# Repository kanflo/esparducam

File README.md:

# Esparducam
#### A low cost network camera for the ESP8266

This repository contains code and schematics to build a development board joining the ESP8266 with the [Arducam Mini](http://www.arducam.com/arducam-mini-released/) module. Build surveillance cameras, read your water meter, attach one to your kite.

The board design allows for small breakout boards to be attached. There currently is [a breakout board the the RFM69C](https://github.com/kanflo/esparducam/tree/master/hardware/ism-boardlet), [an ESP12 board with pogo pins](https://github.com/kanflo/esparducam/tree/master/hardware/esp-pinlet) and [one for swappable ESP12 modules](https://github.com/kanflo/esparducam/tree/master/hardware/esp-boardlet).

Oh, the accompanying blog posts are [here](http://johan.kanflo.com/building-a-low-cost-wifi-camera/), [here](http://johan.kanflo.com/a-versatile-esp8266-development-board/) and [here](http://johan.kanflo.com/esparducam-mini/).

### Usage

Clone the ESP Open RTOS repository. See the documentation for how to add your SSID name and password.

```
git clone --recursive https://github.com/Superhouse/esp-open-rtos.git
```

Add nedded extra modules to ESP Open RTOS ("EOR"):

```
cd esp-open-rtos/extras
git clone https://github.com/kanflo/eor-spi.git spi
git clone https://github.com/kanflo/eor-http-upload.git http-upload
```

Someday I'll start using the native EOR SPI driver, you have to bear with me for now :)

Set the environment variable ```$EOR_ROOT```to point to your EOR repository:

```
export EOR_ROOT=/path/to/esp-open-rtos
```

Clone this repository, make and flash:

```
git clone --recursive https://github.com/kanflo/esparducam.git
cd esparducam
make -j8 && make flash
```

The repository is preconfigured for the Esparducam board. Check ```config.h``` for building for the Esparducam Mini.

When flashing has completed, open a serial terminal to learn the IP number of your board. Open a web brower, point it to your IP and an image should be captured and displayed. While in the serial terminal, type ```help``` for a list of supported commands.

Start the python script ```server.py``` and type ```upload:<your IP>``` to capture, upload and display an image on your computer.

If you connect a [PIR module](http://www.ebay.com/sch/i.html?_trksid=PIR+module.TRS0&_nkw=PIR+module&_sacat=0) [eBay] to the JST connector of the Esparducam board you can use the command ```motion:on:<your ip>``` to have the board capture and upload an image when motion is detected. The Mini variant has a 3 pin slot for attaching a PIR but you need to check the pinout carefully. It should be VCC, OUT, GND but I have seen other combinations.

### Limitations

This is work in progress and there is currently very little error handling. Simultaneous clients will break the camera demo.

-

Licensed under the MIT license. Have fun!

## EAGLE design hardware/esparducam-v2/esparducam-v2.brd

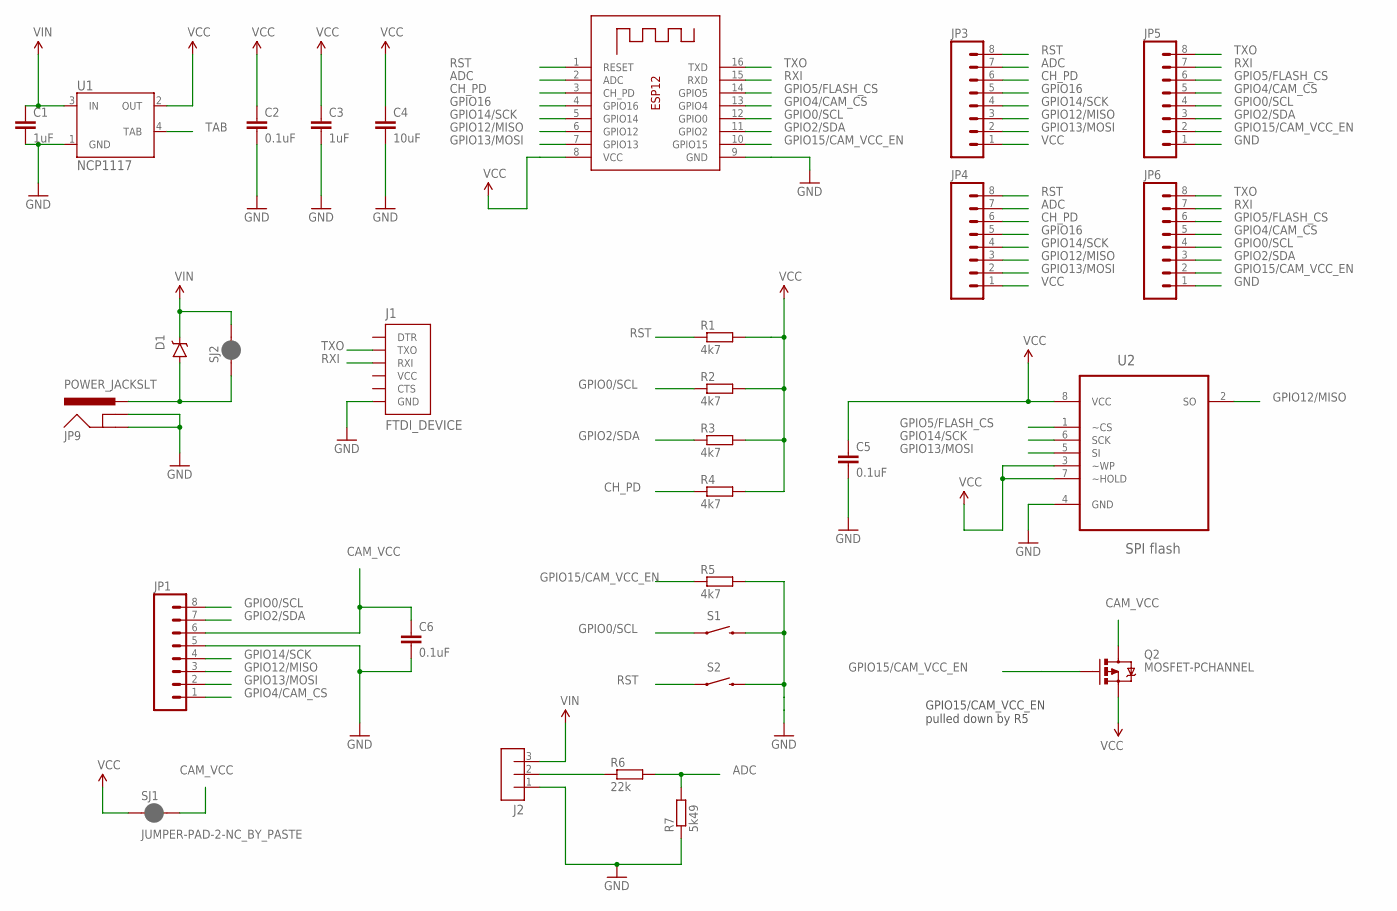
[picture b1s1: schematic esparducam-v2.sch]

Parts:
C1, C3: 1uF; 0603-CAP
C2, C5, C6: 0.1uF; 0603-CAP
C4: 10uF; 0603-CAP
D1: DIODE-SCHOTTKYSOD-123FL; SOD-123FL
J1: FTDI_DEVICE; FTDI
J2: JST_ZH_3PIN
JP1, JP3, JP4, JP5, JP6: M08; 1X08_ROUND
JP9: POWER_JACKSLT; POWER_JACK_SLOT
Q2: MOSFET-PCHANNEL; SOT23-3
R1, R2, R3, R4, R5: 4k7; R0603
R6: 22k; R0603
R7: 5k49; R0603
S1, S2: SWITCH-MOMENTARY-2SMD-1101NE; TACTILE-SWITCH-1101NE
SJ1, SJ2: JUMPER-PAD-2-NC_BY_PASTE; PAD-JUMPER-2-NC_BY_PASTE_YES_SILK
U1: NCP1117; SOT223
U2: SPI flash; SOIC127P600X175-8N
X1: ESP-12

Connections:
ADC: JP3.7, JP4.7, R6.2, R7.2, X1.2 (ADC)
CAM_VCC: C6.1, JP1.6, Q2.3 (D), SJ1.2
CH_PD: JP3.6, JP4.6, R4.1, X1.3 (CH_PD)
GND: C1.2, C2.2, C3.2, C4.2, C5.2, C6.2, J1.GND, J2.1, JP1.5, JP5.1, JP6.1, JP9.GND@1 (GNDBREAK), JP9.GND@2 (GND), R5.2, R7.1, S1.2, S2.2, U1.1 (GND), U2.4 (GND), X1.9 (GND)
GPIO0/SCL: JP1.8, JP5.4, JP6.4, R2.1, S1.1, X1.12 (GPIO0)
GPIO2/SDA: JP1.7, JP5.3, JP6.3, R3.1, X1.11 (GPIO2)
GPIO4/CAM_CS: JP1.1, JP5.5, JP6.5, X1.13 (GPIO4)
GPIO5/FLASH_CS: JP5.6, JP6.6, U2.1 (~CS), X1.14 (GPIO5)
GPIO12/MISO: JP1.3, JP3.3, JP4.3, U2.2 (SO), X1.6 (GPIO12)
GPIO13/MOSI: JP1.2, JP3.2, JP4.2, U2.5 (SI), X1.7 (GPIO13)
GPIO14/SCK: JP1.4, JP3.4, JP4.4, U2.6 (SCK), X1.5 (GPIO14)
GPIO15/CAM_VCC_EN: JP5.2, JP6.2, Q2.1 (G), R5.1, X1.10 (GPIO15)
GPIO16: JP3.5, JP4.5, X1.4 (GPIO16)
unnamed: J2.2, R6.1
unnamed: D1.A, JP9.PWR, SJ2.1
RST: JP3.8, JP4.8, R1.1, S2.1, X1.1 (RESET)
RXI: J1.RXI, JP5.7, JP6.7, X1.15 (RXD)
TAB: U1.4 (TAB)
TXO: J1.TXO, JP5.8, JP6.8, X1.16 (TXD)
VCC: C2.1, C3.1, C4.1, C5.1, JP3.1, JP4.1, Q2.2 (S), R1.2, R2.2, R3.2, R4.2, SJ1.1, U1.2 (OUT), U2.3 (~WP), U2.7 (~HOLD), U2.8 (VCC), X1.8 (VCC)
VIN: C1.1, D1.C, J2.3, SJ2.2, U1.3 (IN)

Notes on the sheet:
GPIO15/CAM_VCC_EN pulled down by R5

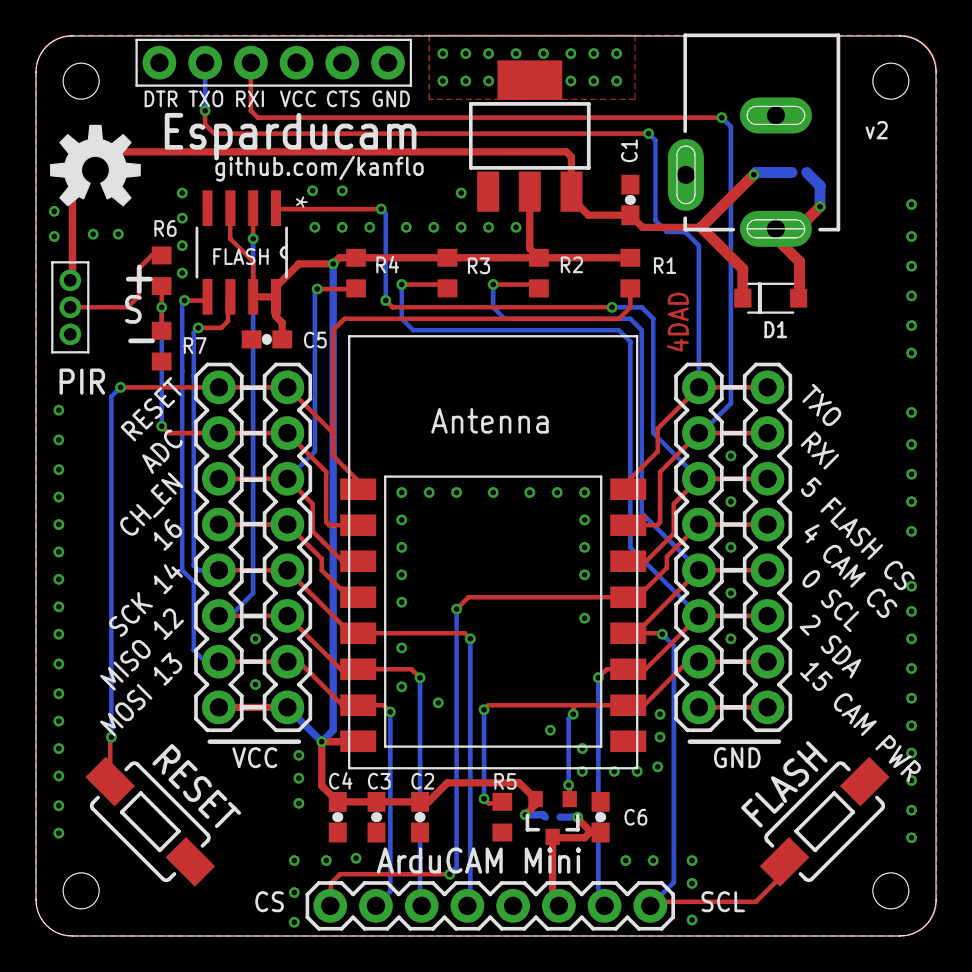
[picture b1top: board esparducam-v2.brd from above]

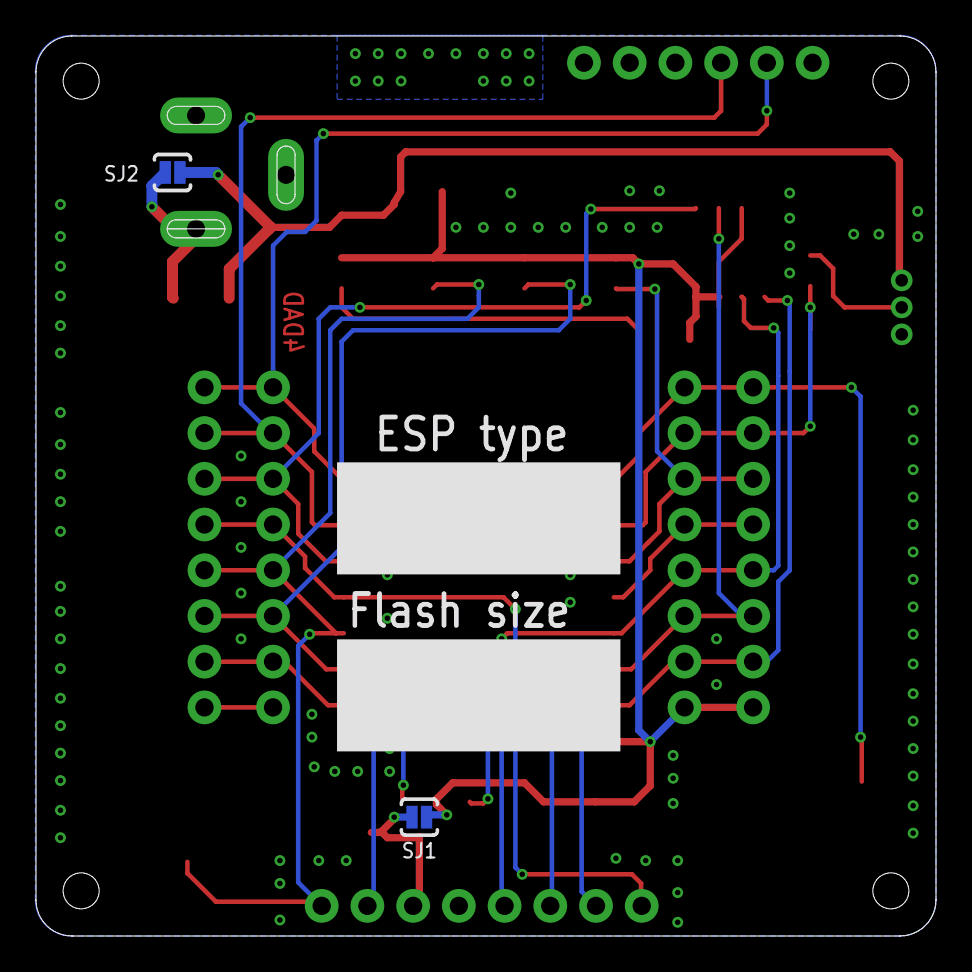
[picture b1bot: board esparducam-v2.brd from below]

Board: 2 copper layers, 50.0 x 50.0 mm, 31 parts (2 on the bottom side), 20 nets.

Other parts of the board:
U$1: OSHW-LOGO-M

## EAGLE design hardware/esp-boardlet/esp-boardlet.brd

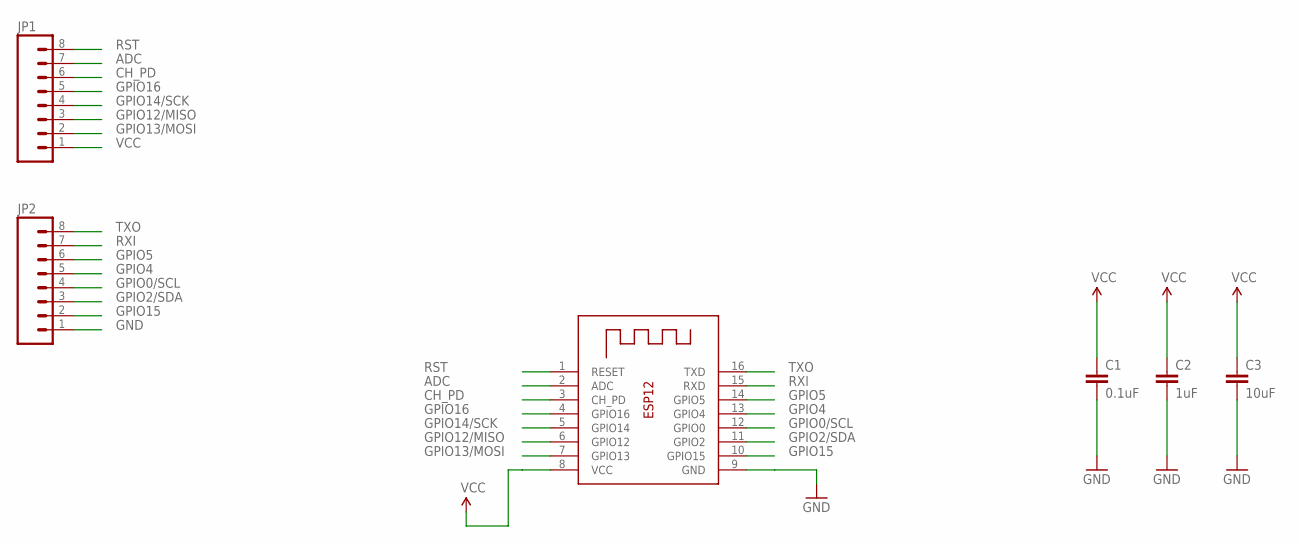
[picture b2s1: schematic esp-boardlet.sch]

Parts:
C1: 0.1uF; 0603-CAP
C2: 1uF; 0603-CAP
C3: 10uF; 0603-CAP
JP1, JP2: M08; 1X08_ROUND
X1: ESP-12

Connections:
ADC: JP1.7, X1.2 (ADC)
CH_PD: JP1.6, X1.3 (CH_PD)
GND: C1.2, C2.2, C3.2, JP2.1, X1.9 (GND)
GPIO0/SCL: JP2.4, X1.12 (GPIO0)
GPIO2/SDA: JP2.3, X1.11 (GPIO2)
GPIO4: JP2.5, X1.13 (GPIO4)
GPIO5: JP2.6, X1.14 (GPIO5)
GPIO12/MISO: JP1.3, X1.6 (GPIO12)
GPIO13/MOSI: JP1.2, X1.7 (GPIO13)
GPIO14/SCK: JP1.4, X1.5 (GPIO14)
GPIO15: JP2.2, X1.10 (GPIO15)
GPIO16: JP1.5, X1.4 (GPIO16)
RST: JP1.8, X1.1 (RESET)
RXI: JP2.7, X1.15 (RXD)
TXO: JP2.8, X1.16 (TXD)
VCC: C1.1, C2.1, C3.1, JP1.1, X1.8 (VCC)

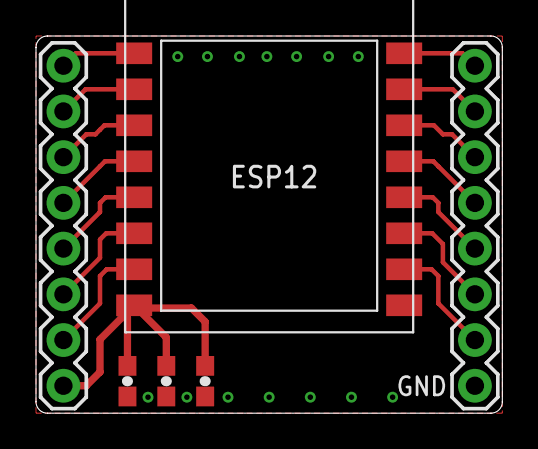
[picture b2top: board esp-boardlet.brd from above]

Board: 2 copper layers, 25.9 x 21.0 mm, 7 parts (1 on the bottom side), 16 nets.

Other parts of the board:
U$1: OSHW-LOGO-M

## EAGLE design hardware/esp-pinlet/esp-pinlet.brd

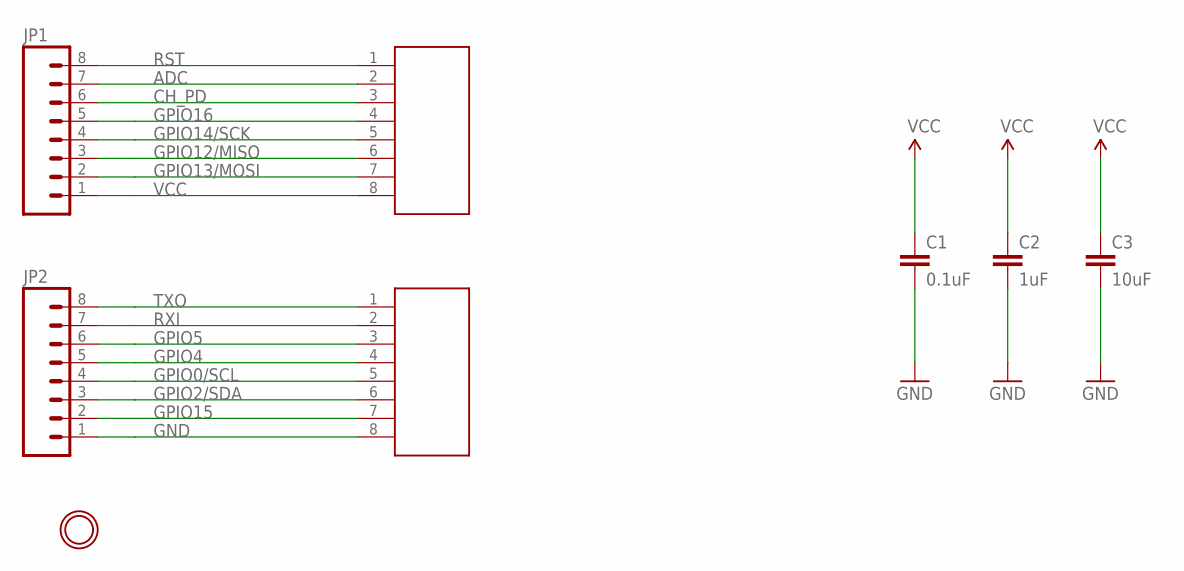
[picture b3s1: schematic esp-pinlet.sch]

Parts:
C1: 0.1uF; 0603-CAP
C2: 1uF; 0603-CAP
C3: 10uF; 0603-CAP
JP1, JP2: M08; 1X08_ROUND
U$2, U$3: 82XMM_POGO_PIN; 8X2MM_POGO_PIN
U$6: MOUNTINGHOLE2.0; MOUNTINGHOLE_2.0_PLATED

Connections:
ADC: JP1.7, U$2.2
CH_PD: JP1.6, U$2.3
GND: C1.2, C2.2, C3.2, JP2.1, U$3.8
GPIO0/SCL: JP2.4, U$3.5
GPIO2/SDA: JP2.3, U$3.6
GPIO4: JP2.5, U$3.4
GPIO5: JP2.6, U$3.3
GPIO12/MISO: JP1.3, U$2.6
GPIO13/MOSI: JP1.2, U$2.7
GPIO14/SCK: JP1.4, U$2.5
GPIO15: JP2.2, U$3.7
GPIO16: JP1.5, U$2.4
RST: JP1.8, U$2.1
RXI: JP2.7, U$3.2
TXO: JP2.8, U$3.1
VCC: C1.1, C2.1, C3.1, JP1.1, U$2.8

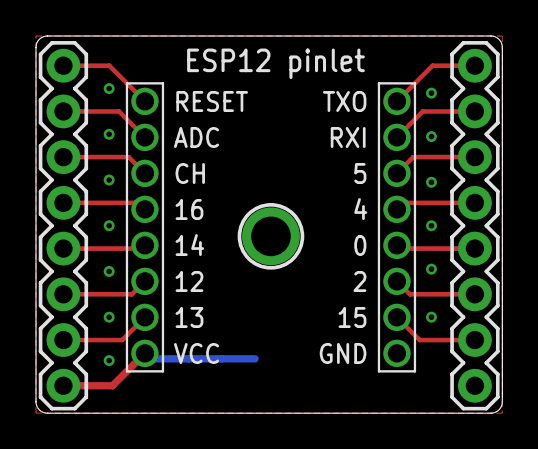
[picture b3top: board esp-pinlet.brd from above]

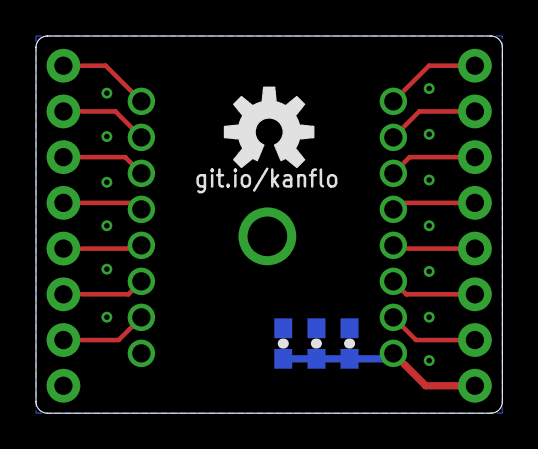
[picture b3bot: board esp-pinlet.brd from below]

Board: 2 copper layers, 25.9 x 21.0 mm, 9 parts (4 on the bottom side), 16 nets.

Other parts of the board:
U$1: OSHW-LOGO-M

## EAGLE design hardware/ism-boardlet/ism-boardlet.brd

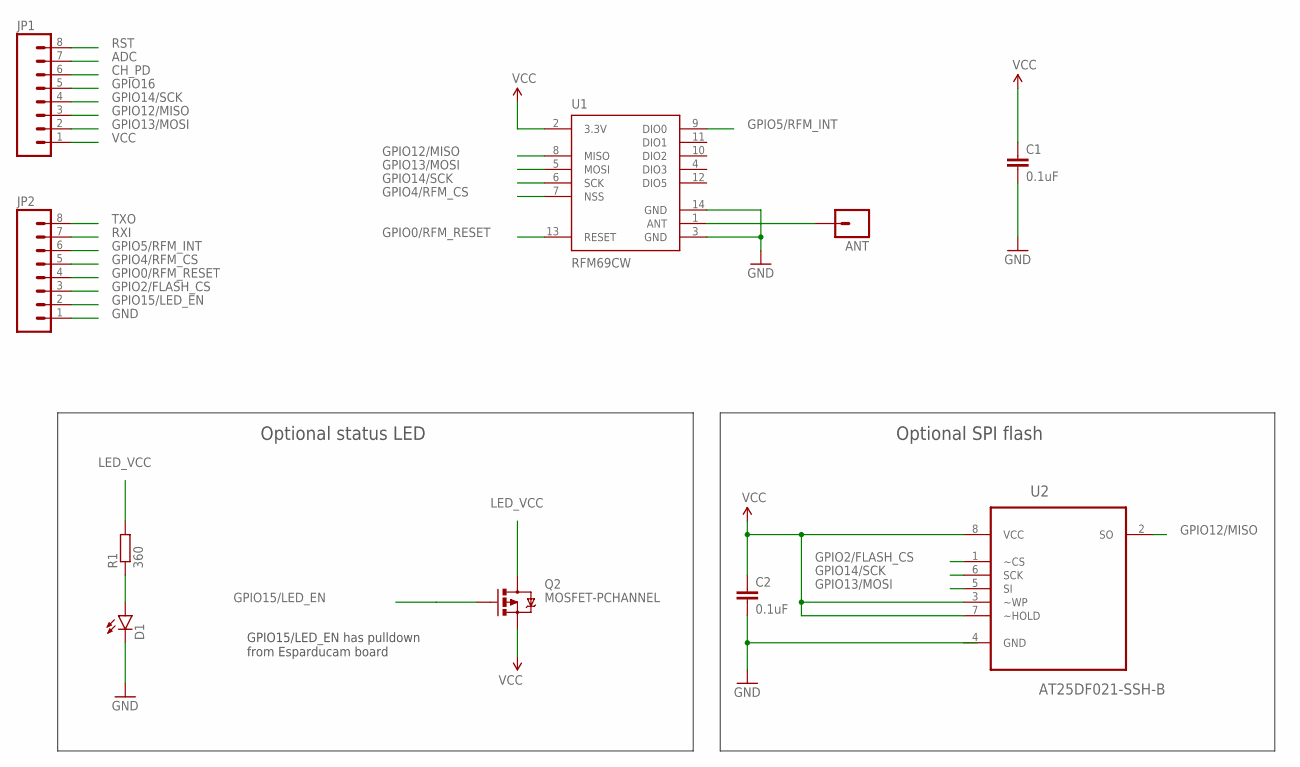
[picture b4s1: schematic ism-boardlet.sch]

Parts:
ANT: M01PTH; 1X01
C1, C2: 0.1uF; 0603-CAP
D1: LED0603; LED-0603
JP1, JP2: M08; 1X08_ROUND
Q2: MOSFET-PCHANNEL; SOT23-3
R1: 360; R0603
U1: RFM69CW; RFM69CW-XXXS2
U2: AT25DF021-SSH-B; SOIC127P600X175-8N

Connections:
ADC: JP1.7
CH_PD: JP1.6
GND: C1.2, C2.2, D1.C, JP2.1, U1.3 (GND), U1.14 (GND)
GPIO0/RFM_RESET: JP2.4, U1.13 (RESET)
GPIO2/FLASH_CS: JP2.3, U2.1 (~CS)
GPIO4/RFM_CS: JP2.5, U1.7 (NSS)
GPIO5/RFM_INT: JP2.6, U1.9 (DIO0)
GPIO12/MISO: JP1.3, U1.8 (MISO), U2.2 (SO)
GPIO13/MOSI: JP1.2, U1.5 (MOSI), U2.5 (SI)
GPIO14/SCK: JP1.4, U1.6 (SCK), U2.6 (SCK)
GPIO15/LED_EN: JP2.2, Q2.1 (G)
GPIO16: JP1.5
LED_VCC: Q2.3 (D), R1.2
unnamed: D1.A, R1.1
unnamed: ANT.1, U1.1 (ANT)
RST: JP1.8
RXI: JP2.7
TXO: JP2.8
VCC: C1.1, C2.1, JP1.1, Q2.2 (S), U1.2 (3.3V), U2.3 (~WP), U2.7 (~HOLD), U2.8 (VCC)

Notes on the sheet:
GPIO15/LED_EN has pulldown from Esparducam board
Optional status LED
Optional SPI flash

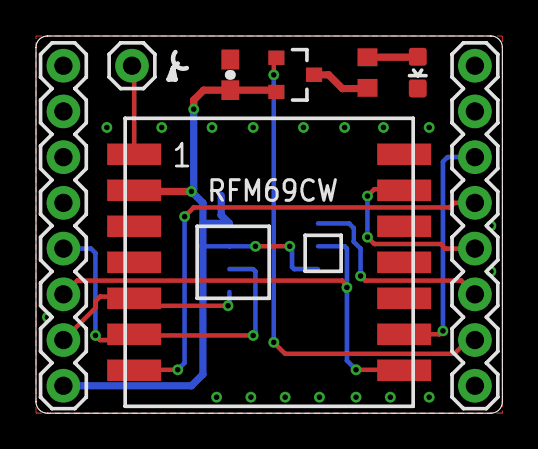
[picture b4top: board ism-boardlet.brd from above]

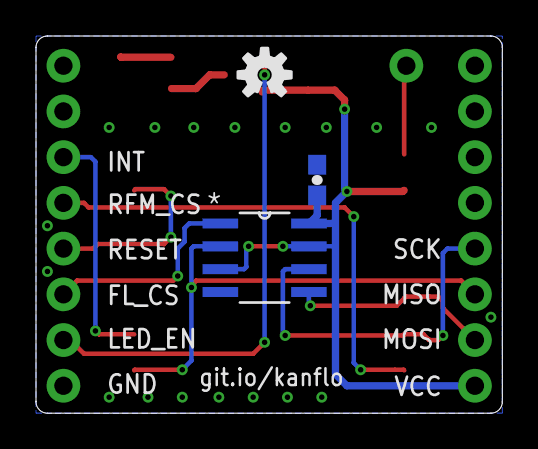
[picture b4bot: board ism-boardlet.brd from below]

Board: 2 copper layers, 25.9 x 21.0 mm, 11 parts (3 on the bottom side), 13 nets.

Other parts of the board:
U$2: OSHW-LOGO-S

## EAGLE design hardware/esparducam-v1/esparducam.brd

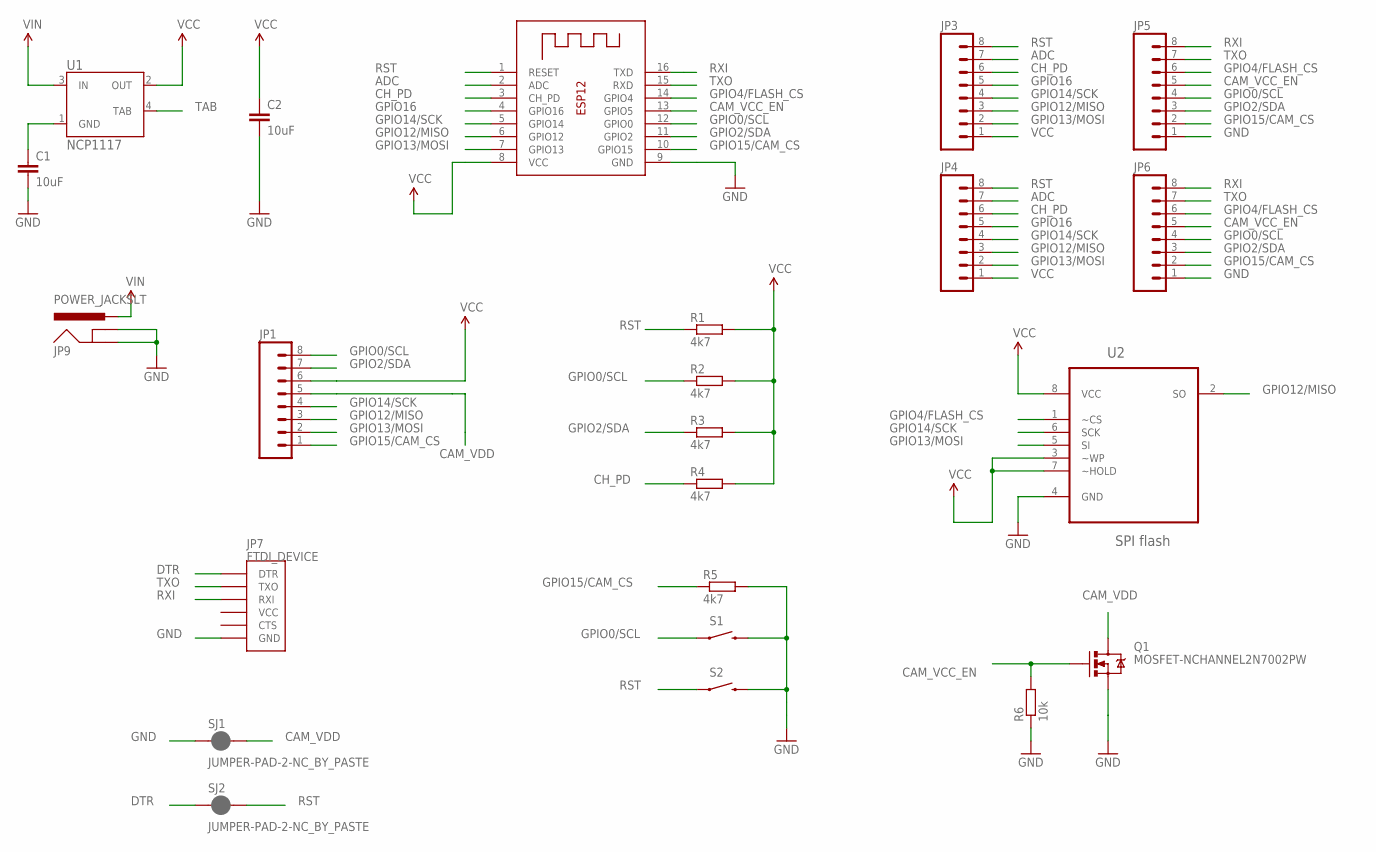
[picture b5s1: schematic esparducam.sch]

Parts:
C1, C2: 10uF; 0603-CAP
JP1, JP3, JP4, JP5, JP6: M08; 1X08_ROUND
JP7: FTDI_DEVICE; FTDI_DEVICE_SIDE
JP9: POWER_JACKSLT; POWER_JACK_SLOT
Q1: MOSFET-NCHANNEL2N7002PW; SOT323
R1, R2, R3, R4, R5: 4k7; R0603
R6: 10k; R0603
S1, S2: SWITCH-MOMENTARY-2SMD-1101NE; TACTILE-SWITCH-1101NE
SJ1, SJ2: JUMPER-PAD-2-NC_BY_PASTE; PAD-JUMPER-2-NC_BY_PASTE_YES_SILK
U1: NCP1117; SOT223
U2: SPI flash; SOIC127P600X175-8N
X1: ESP-12

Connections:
ADC: JP3.7, JP4.7, X1.2 (ADC)
CAM_VCC_EN: JP5.5, JP6.5, Q1.1 (G), R6.2, X1.13 (GPIO5)
CAM_VDD: JP1.5, Q1.3 (D), SJ1.2
CH_PD: JP3.6, JP4.6, R4.1, X1.3 (CH_PD)
DTR: JP7.P$1 (DTR), SJ2.1
GND: C1.2, C2.2, JP5.1, JP6.1, JP7.P$6 (GND), JP9.GND@1 (GNDBREAK), JP9.GND@2 (GND), Q1.2 (S), R5.2, R6.1, S1.2, S2.2, SJ1.1, U2.4 (GND), X1.9 (GND)
GPIO0/SCL: JP1.8, JP5.4, JP6.4, R2.1, S1.1, X1.12 (GPIO0)
GPIO2/SDA: JP1.7, JP5.3, JP6.3, R3.1, X1.11 (GPIO2)
GPIO4/FLASH_CS: JP5.6, JP6.6, U2.1 (~CS), X1.14 (GPIO4)
GPIO12/MISO: JP1.3, JP3.3, JP4.3, U2.2 (SO), X1.6 (GPIO12)
GPIO13/MOSI: JP1.2, JP3.2, JP4.2, U2.5 (SI), X1.7 (GPIO13)
GPIO14/SCK: JP1.4, JP3.4, JP4.4, U2.6 (SCK), X1.5 (GPIO14)
GPIO15/CAM_CS: JP1.1, JP5.2, JP6.2, R5.1, X1.10 (GPIO15)
GPIO16: JP3.5, JP4.5, X1.4 (GPIO16)
unnamed: C1.1, U1.1 (GND)
RST: JP3.8, JP4.8, R1.1, S2.1, SJ2.2, X1.1 (RESET)
RXI: JP5.8, JP6.8, JP7.P$3 (RXI), X1.16 (TXD)
TAB: U1.4 (TAB)
TXO: JP5.7, JP6.7, JP7.P$2 (TXO), X1.15 (RXD)
VCC: C2.1, JP1.6, JP3.1, JP4.1, R1.2, R2.2, R3.2, R4.2, U1.2 (OUT), U2.3 (~WP), U2.7 (~HOLD), U2.8 (VCC), X1.8 (VCC)
VIN: JP9.PWR, U1.3 (IN)

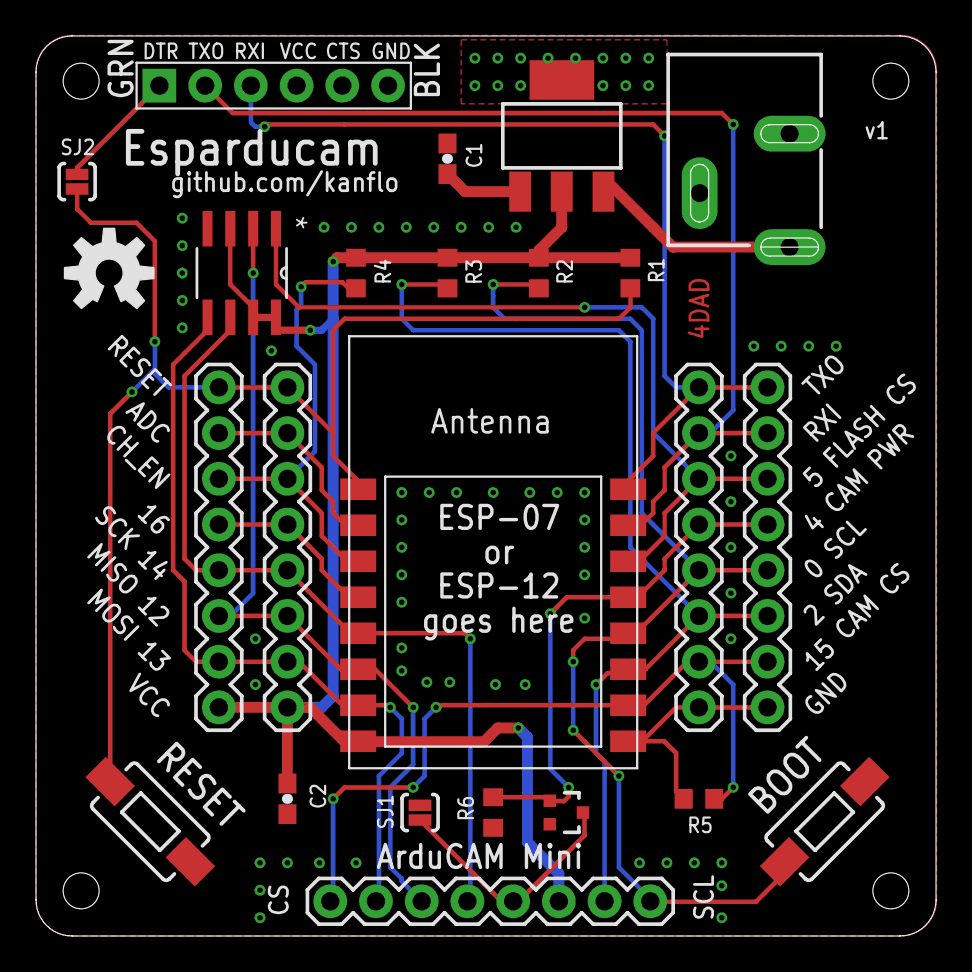
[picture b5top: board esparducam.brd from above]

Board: 2 copper layers, 50.0 x 50.0 mm, 24 parts (0 on the bottom side), 20 nets.

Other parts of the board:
U$1: OSHW-LOGO-M

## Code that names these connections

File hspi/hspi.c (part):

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
/// @brief HSPI Initiaization - with automatic chip sellect
/// Pins:
/// 	MISO GPIO12
/// 	MOSI GPIO13
/// 	CLK GPIO14
/// 	CS GPIO15
/// 	DC GPIO2
/// @return  void
void hspi_init(uint16_t prescale)
{
    WRITE_PERI_REG(PERIPHS_IO_MUX, 0x105);        //clear bit9

    PIN_FUNC_SELECT(PERIPHS_IO_MUX_MTDI_U, 2);    // HSPIQ MISO GPIO12
    PIN_FUNC_SELECT(PERIPHS_IO_MUX_MTCK_U, 2);    // HSPID MOSI GPIO13
    PIN_FUNC_SELECT(PERIPHS_IO_MUX_MTMS_U, 2);    // CLK        GPIO14

#ifdef SOFTCS
/* Enable GPIO on the specified pin, and set it to input/output/ with
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//    PIN_FUNC_SELECT(PERIPHS_IO_MUX_MTDO_U, FUNC_GPIO15);
    //gpio_write(GPIO_ID_PIN(15),1);
#else
    PIN_FUNC_SELECT(PERIPHS_IO_MUX_MTDO_U, 2);    // CS         GPIO15
#endif

// SPI clock = CPU clock / 10 / 4
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
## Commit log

2015-07-23 Added .gitignore for local.h
2015-07-23 Working webcam prototype. Flash and connect to port 80.
2015-07-23 Updated i2c driver
2015-11-03 Ain't pretty but it works!
2015-11-03 Removed the local i2c module
2015-11-03 Bugfix
2015-11-03 Removed HSPI
2015-11-03 Updated gitignore
2015-11-03 Cleanup
2015-11-03 Added FreeRTOS config for IRQ driven UART RX
2015-11-17 Added schematics and gerbers for the v1 board.
2015-11-17 Verification plan for the v1 board.
2015-11-17 More cleanup.
2015-11-17 HW cleanup
2015-11-17 Changed reivsion label on schematic.
2015-12-03 Verification updates
2015-12-03 Version 2 of the Esparducam board
2016-01-02 Esparducam board v2
2016-01-03 Added envvar EOR_ROOT Makefile cleanup
2016-01-09 Makefile cleanup
2016-01-09 Added camera power cycle Removed the 1s delay at start
2016-01-21 Added CLI Added python server to receive image uploads
2016-01-21 Bugfix, a weird one...
2016-01-21 ESP12 breakout board, untested
2016-01-21 RFM69C addon board
2016-01-21 Added board image
2016-01-21 Added readme and license
2016-01-21 Pogo pin addon board
2016-01-21 Support for changing JPEG size.
2016-01-21 Updated docs
2016-01-21 Added motion cli command
2016-01-21 Added shameless link to own blog
2016-02-01 Added gerbers for pinlet. NOTE! Gerbers have not been produced but looks ok on circuitpeople.com
2016-02-21 Updated 'help' command
2016-05-21 Fixed git clone typo.
2016-06-02 Added missing dependency.
2016-07-19 Now with OTA
2016-11-13 Updated value for C6
2016-11-13 Removed unused module
2016-11-13 Updated FreeRTOS API
2016-11-13 Updated FreeRTOS API (again)
2017-04-16 Fix broken Markdown headings
2017-09-17 Esparducam Mini support
2017-09-20 Fixed code rot, compatible with latest EOR
2017-10-03 Fixed server task stack size Added uHej for service discovery
2017-10-06 Updated uhej module
2017-10-07 Updates needed for latest EOR master
2017-10-07 Server tells you your IP
2017-12-06 Fixed #4

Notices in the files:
hspi/hspi.c:
@par Copyright © 2015 Sem
@par Copyright © 2015 Mike Gore, GPL License
@par You are free to use this code under the terms of GPL
This is free software: you can redistribute it and/or modify it under the
terms of the GNU General Public License as published by the Free Software
parts and their libraries:
SparkFun-Connectors: Licensing: Creative Commons ShareAlike 4.0 International - https://creativecommons.org/licenses/by-sa/4.0
microbuilder: This work is placed in the public domain, and may be freely used for commercial and non-commercial work with the following conditions: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
